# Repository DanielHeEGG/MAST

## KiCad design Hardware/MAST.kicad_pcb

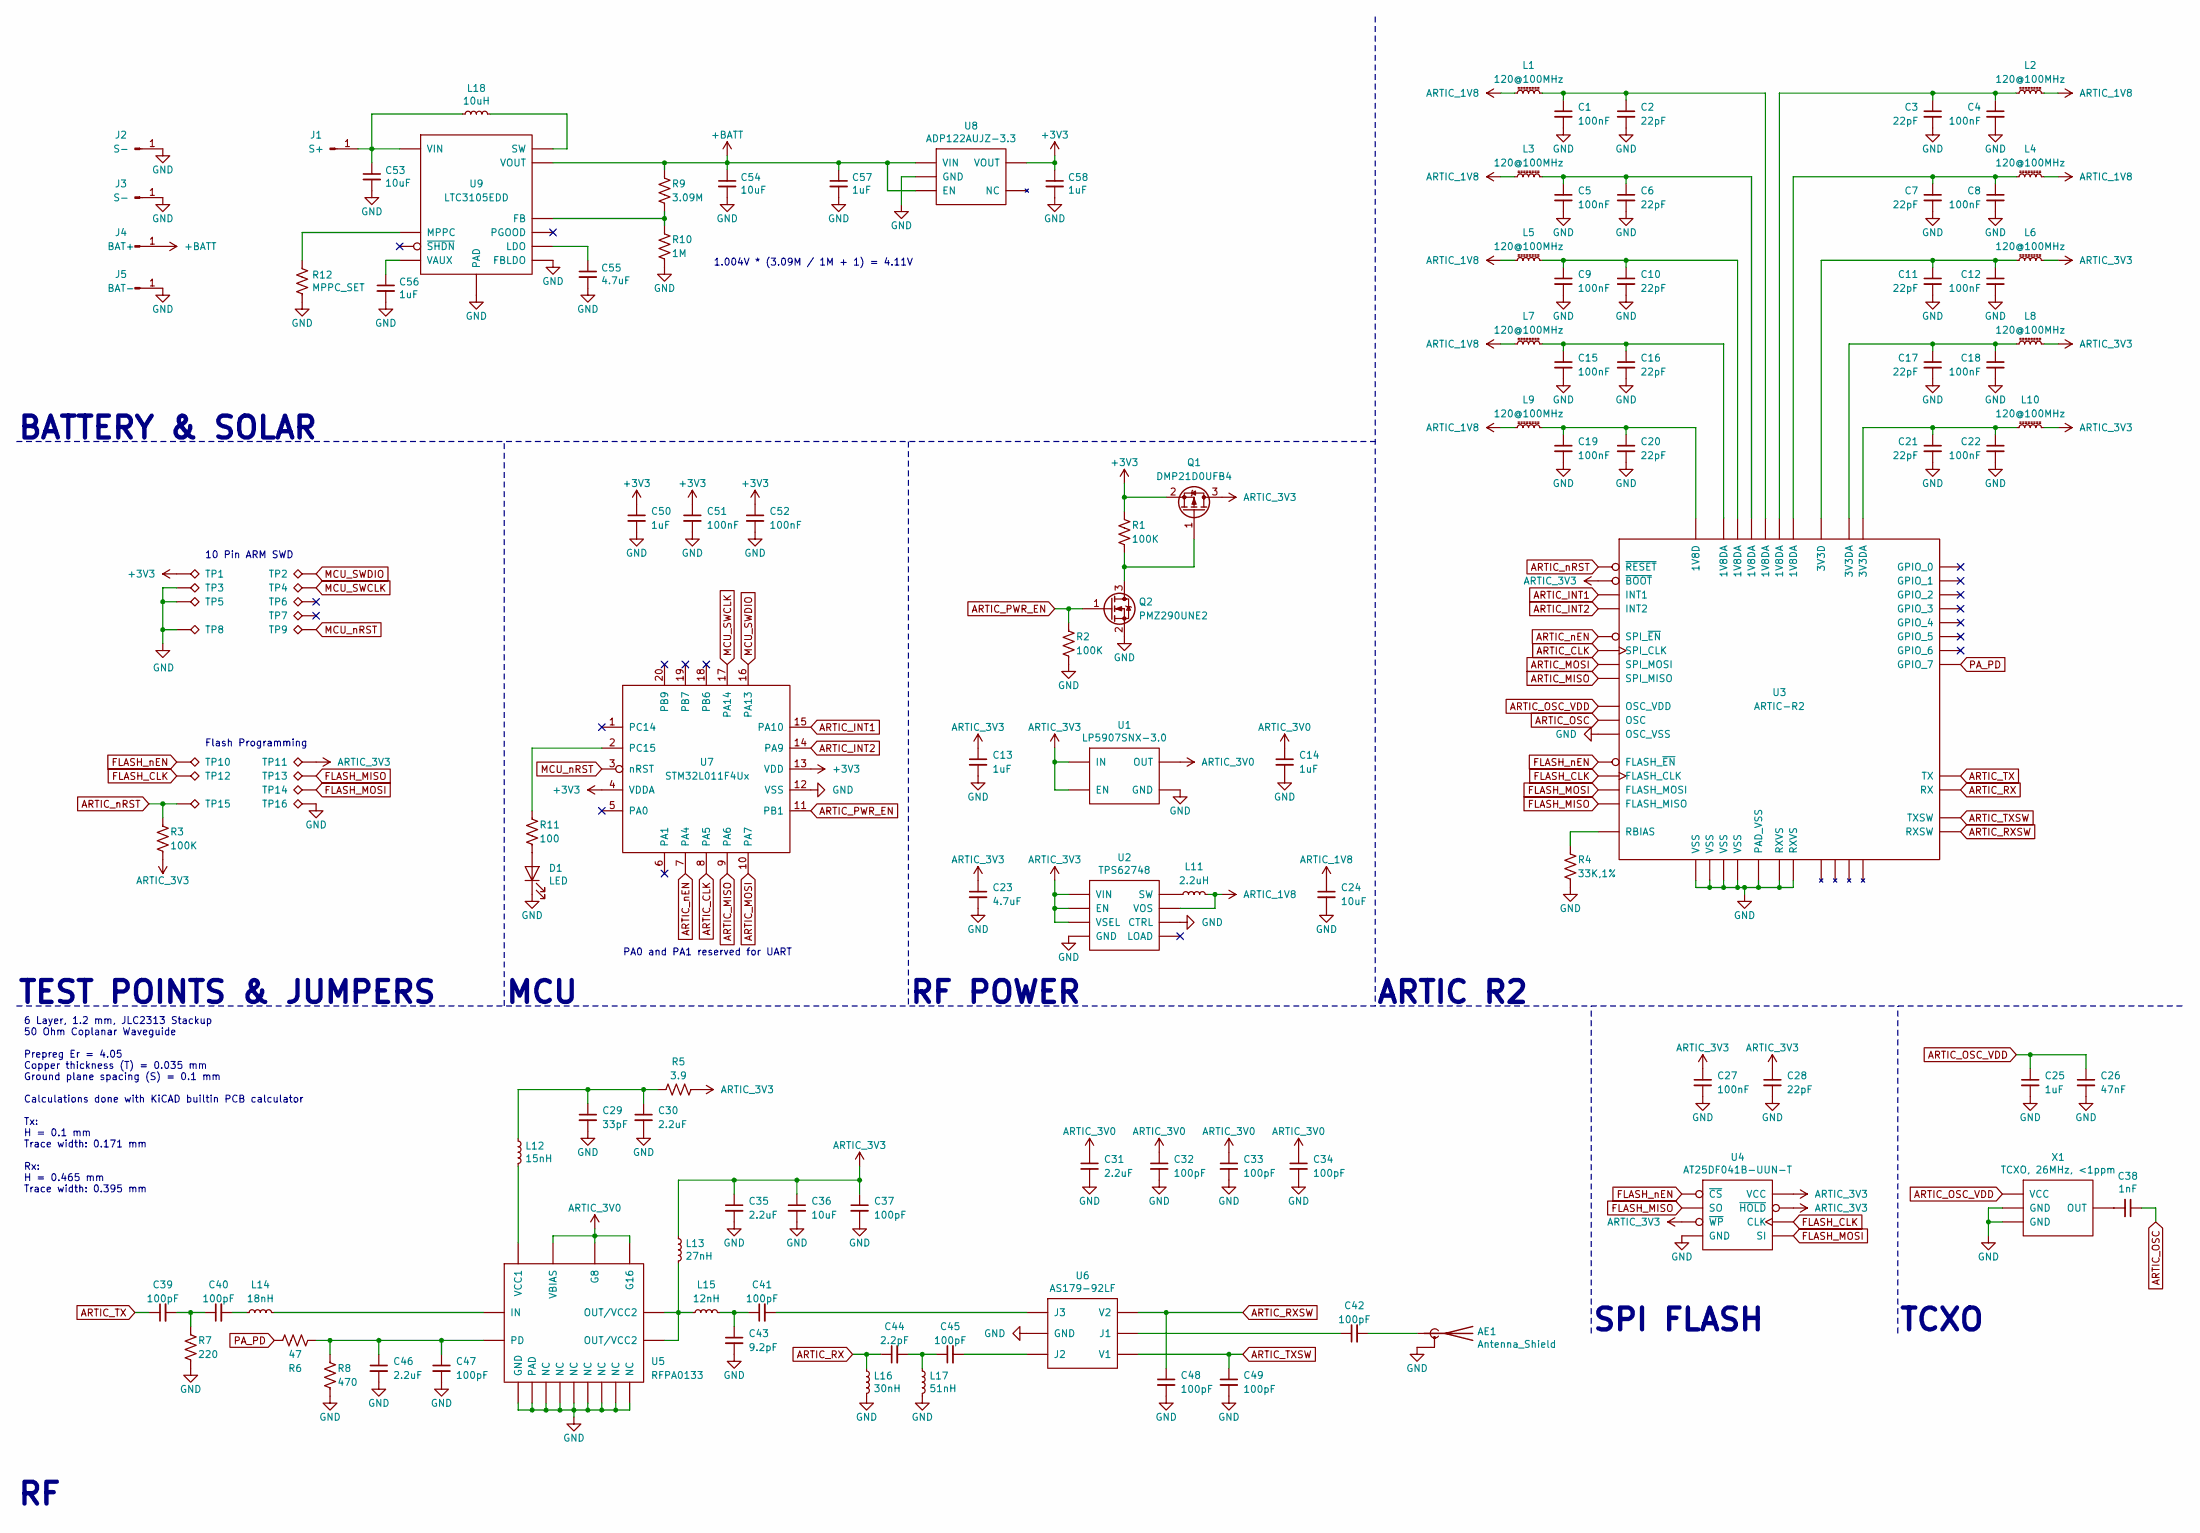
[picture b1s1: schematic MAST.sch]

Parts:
AE1: Antenna_Shield; U.FL_Hirose_U.FL-R-SMT-1_Vertical; Part# U.FL-R-SMT-1(10); Digikey# H11891TR-ND
C1, C4, C5, C8, C9, C12, C15, C18, C19, C22, C27, C51, C52: 100nF; C_0201_0603Metric; Part# CC0201MRX5R5BB104; LCSC# C277512
C2, C3, C6, C7, C10, C11, C16, C17, C20, C21, C28: 22pF; C_0201_0603Metric; Part# CC0201GRNPO9BN220; Digikey# 311-3681-2-ND
C13, C14, C25, C50, C56, C57, C58: 1uF; C_0201_0603Metric; Part# CC0201MRX5R5BB105; Digikey# 311-1613-2-ND
C23, C55: 4.7uF; C_0402_1005Metric; Part# CC0402KRX5R6BB475; Digikey# 311-3477-2-ND
C24, C36, C53, C54: 10uF; C_0402_1005Metric; Part# CC0402MRX5R6BB106; Digikey# 311-3480-2-ND
C26: 47nF; C_0201_0603Metric; Part# CC0201KRX5R6BB473; Digikey# 13-CC0201KRX5R6BB473TR-ND
C29: 33pF; C_0201_0603Metric; Part# CC0201JRNPO8BN330; Digikey# 311-1381-2-ND
C30, C31, C35, C46: 2.2uF; C_0402_1005Metric; Part# CC0402MRX5R6BB225; Digikey# 311-1733-2-ND
C32, C33, C34, C37, C39, C40, C41, C42, C45, C47, C48, C49: 100pF; C_0201_0603Metric; Part# CC0201JRNPO8BN101; Digikey# 311-1382-2-ND
C38: 1nF; C_0201_0603Metric; Part# CC0201KRX7R7BB102; Digikey# 311-1399-2-ND
C43: 9.2pF; C_0201_0603Metric; Part# GJM0335C1E9R2CB01D; Digikey# 490-17292-2-ND
C44: 2.2pF; C_0201_0603Metric; Part# CC0201BRNPO8BN2R2; Digikey# 311-3289-2-ND
D1: LED; LED_0402_1005Metric; Part# 16-213/SURC/S530-A3/TR8; LCSC# C136765
J1: S+; EP_5x2mm
J2, J3: S-; EP_3x2mm
J4: BAT+; EP_3x2mm
J5: BAT-; EP_3x2mm
L1, L2, L3, L4, L5, L6, L7, L8, L9, L10: 120@100MHz; L_0201_0603Metric; Part# BLM03AG121SN1D; Digikey# 490-2557-2-ND
L11: 2.2uH; L_0805_2012Metric; Part# LQM21PN2R2MC0D; Digikey# 490-4994-2-ND
L12: 15nH; L_0201_0603Metric; Part# LQP03TG15NJ02D; Digikey# 490-12895-2-ND
L13: 27nH; L_0201_0603Metric; Part# LQP03TG27NJ02D; Digikey# 490-12942-2-ND
L14: 18nH; L_0201_0603Metric; Part# LQP03TG18NJ02D; Digikey# 490-12896-2-ND
L15: 12nH; L_0201_0603Metric; Part# LQP03TG12NJ02D; Digikey# 490-12894-2-ND
L16: 30nH; L_0201_0603Metric; Part# LQP03TN30NH02D; Digikey# 490-13005-2-ND
L17: 51nH; L_0201_0603Metric; Part# LQP03TN51NH02D; Digikey# 490-13014-2-ND
L18: 10uH; L_0805_2012Metric; Part# LQM21FN100M80L; Digikey# 490-6682-2-ND
Q1: DMP21D0UFB4; SOT-883; Part# DMP21D0UFB4-7B; Digikey# DMP21D0UFB4-7BDITR-ND
Q2: PMZ290UNE2; SOT-883; Part# PMZ290UNE2YL; Digikey# 1727-2233-2-ND
R1, R2, R3: 100K; R_0201_0603Metric; Part# AC0201FR-07100KL; Digikey# YAG3411TR-ND
R4: 33K,1%; R_0201_0603Metric; Part# RC0201FR-0733KL; Digikey# YAG2282TR-ND
R5: 3.9; R_0402_1005Metric; Part# RC0402FR-073R9L; Digikey# 13-RC0402FR-073R9LTR-ND
R6: 47; R_0402_1005Metric; Part# RC0402FR-0747RL; Digikey# 311-47.0LRTR-ND
R7: 220; R_0201_0603Metric; Part# RC0201FR-07220KL; Digikey# YAG2277TR-ND
R8: 470; R_0402_1005Metric; Part# RC0402FR-07470RL; Digikey# 311-470LRTR-ND
R9: 3.09M; R_0201_0603Metric; Part# RC0201FR-073M09L; Digikey# RC0201FR-073M09L-ND
R10: 1M; R_0201_0603Metric; Part# RC0201FR-071ML; Digikey# 311-1MMTR-ND
R11: 100; R_0402_1005Metric; Part# RC0402JR-07100RL; Digikey# 311-100JRTR-ND
R12: MPPC_SET; R_0603_1608Metric
TP1, TP2, TP3, TP4, TP5, TP6, TP7, TP8, TP9, TP10, TP11, TP12, TP13, TP14, TP15, TP16: TestPoint
U1: LP5907SNX-3.0; Texas_X2SON-4_1x1mm_P0.65mm; Part# LP5907SNX-3.0/NOPB; Digikey# 296-39065-2-ND
U2: TPS62748; Texas_DSBGA-8_0.9x1.9mm_Layout2x4_P0.5mm; Part# TPS62748YFPT; Digikey# 296-43000-2-ND
U3: ARTIC-R2; QFN-48-1EP_7x7mm_P0.5mm_EP5.6x5.6mm
U4: AT25DF041B-UUN-T; WLCSP-8_1.58x1.63x0.35mm_Layout3x5_P0.35x0.4mm_Ball0.25mm_P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
U5: RFPA0133; QFN-16-1EP_3x3mm_P0.5mm_EP1.7x1.7mm; Part# RFPA0133TR7; LCSC# C470930
U6: AS179-92LF; SOT-363_SC-70-6; Part# AS179-92LF; Digikey# 863-1003-2-ND
U7: STM32L011F4Ux; ST_UFQFPN-20_3x3mm_P0.5mm; Part# STM32L011F4U6TR; Digikey# 497-17478-2-ND
U8: ADP122AUJZ-3.3; TSOT-23-5; Part# ADP122AUJZ-3.3-R7; Digikey# ADP122AUJZ-3.3-R7TR-ND
U9: LTC3105EDD; DFN-10-1EP_3x3mm_P0.5mm_EP1.65x2.38mm; Part# LTC3105EDD#TRPBF; Digikey# LTC3105EDD#TRPBFTR-ND
X1: TCXO, 26MHz, <1ppm; Crystal_SMD_2016-4Pin_2.0x1.6mm; Part# ECS-TXO-20CSMV-260-AY-TR; Digikey# 50-ECS-TXO-20CSMV-260-AY-TR-ND

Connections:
+3V3: C50.1, C51.1, C52.1, C58.1, Q1.2 (S), R1.1, TP1.1, U7.4 (VDDA), U7.13 (VDD), U8.5 (VOUT)
+BATT: C54.1, C57.1, J4.1, R9.2, U8.1 (VIN), U8.3 (EN), U9.9 (VOUT)
ARTIC_1V8: C24.1, L1.1, L2.1, L3.1, L4.1, L5.1, L7.1, L9.1, L11.2, U2.C2 (VOS)
ARTIC_3V0: C14.1, C31.1, C32.1, C33.1, C34.1, U1.1 (OUT), U5.12 (G8), U5.13 (G16), U5.16 (VBIAS)
ARTIC_3V3: C13.1, C23.1, C27.1, C28.1, C35.1, C36.1, C37.1, L6.1, L8.1, L10.1, L13.1, Q1.3 (D), R3.2, R5.1, TP11.1, U1.3 (EN), U1.4 (IN), U2.A2 (VIN), U2.B1 (EN), U2.C1 (VSEL), U3.46 (~BOOT), U4.A1 (VCC), U4.C1 (~HOLD), U4.E3 (~WP)
ARTIC_CLK: U3.3 (SPI_CLK), U7.8 (PA5)
ARTIC_INT1: U3.47 (INT1), U7.15 (PA10)
ARTIC_INT2: U3.48 (INT2), U7.14 (PA9)
ARTIC_MISO: U3.5 (SPI_MISO), U7.9 (PA6)
ARTIC_MOSI: U3.4 (SPI_MOSI), U7.10 (PA7)
ARTIC_OSC: C38.1, U3.38 (OSC)
ARTIC_OSC_VDD: C25.1, C26.1, U3.37 (OSC_VDD), X1.4 (VCC)
ARTIC_PWR_EN: Q2.1 (G), R2.1, U7.11 (PB1)
ARTIC_RX: C44.1, L16.1, U3.26 (RX)
ARTIC_RXSW: C48.1, U3.22 (RXSW), U6.6 (V2)
ARTIC_TX: C39.1, U3.34 (TX)
ARTIC_TXSW: C49.1, U3.21 (TXSW), U6.4 (V1)
ARTIC_nEN: U3.2 (SPI_~EN), U7.7 (PA4)
ARTIC_nRST: R3.1, TP15.1, U3.1 (~RESET)
FLASH_CLK: TP12.1, U3.12 (FLASH_CLK), U4.E1 (CLK)
FLASH_MISO: TP13.1, U3.14 (FLASH_MISO), U4.C3 (SO)
FLASH_MOSI: TP14.1, U3.13 (FLASH_MOSI), U4.D2 (SI)
FLASH_nEN: TP10.1, U3.15 (FLASH_~EN), U4.A3 (~CS)
GND: AE1.2 (Shield), C1.2, C2.2, C3.2, C4.2, C5.2, C6.2, C7.2, C8.2, C9.2, C10.2, C11.2, C12.2, C13.2, C14.2, C15.2, C16.2, C17.2, C18.2, C19.2, C20.2, C21.2, C22.2, C23.2, C24.2, C25.2, C26.2, C27.2, C28.2, C29.2, C30.2, C31.2, C32.2, C33.2, C34.2, C35.2, C36.2, C37.2, C43.2, C46.2, C47.2, C48.2, C49.2, C50.2, C51.2, C52.2, C53.2, C54.2, C55.2, C56.2, C57.2, C58.2, D1.1 (K), J2.1, J3.1, J5.1, L16.2, L17.2, Q2.2 (S), R2.2, R4.2, R7.1, R8.1, R10.1, R12.2, TP3.1, TP5.1, TP8.1, TP16.1, U1.2 (GND), U1.5, U2.B2 (GND), U2.D1 (CTRL), U3.25 (RXVS), U3.27 (RXVS), U3.29 (VSS), U3.30 (VSS), U3.31 (VSS), U3.32 (VSS), U3.39 (OSC_VSS), U3.49 (PAD_VSS), U4.B2 (GND), U5.1 (NC), U5.2 (GND), U5.4 (NC), U5.5 (NC), U5.7 (NC), U5.8 (NC), U5.11 (NC), U5.15 (NC), U5.17 (PAD), U6.2 (GND), U7.12 (VSS), U8.2 (GND), U9.3 (FBLDO), U9.11 (PAD), X1.1 (GND), X1.2 (GND)
MCU_SWCLK: TP4.1, U7.17 (PA14)
MCU_SWDIO: TP2.1, U7.16 (PA13)
MCU_nRST: TP9.1, U7.3 (nRST)
unnamed: AE1.1 (A), C42.2
unnamed: C1.1, C2.1, L1.2, U3.33 (1V8DA)
unnamed: C3.1, C4.1, L2.2, U3.35 (1V8DA)
unnamed: C5.1, C6.1, L3.2, U3.28 (1V8DA)
unnamed: C7.1, C8.1, L4.2, U3.40 (1V8DA)
unnamed: C9.1, C10.1, L5.2, U3.24 (1V8DA)
unnamed: C11.1, C12.1, L6.2, U3.9 (3V3D)
unnamed: C15.1, C16.1, L7.2, U3.20 (1V8DA)
unnamed: C17.1, C18.1, L8.2, U3.23 (3V3DA)
unnamed: C19.1, C20.1, L9.2, U3.6 (1V8D)
unnamed: C21.1, C22.1, L10.2, U3.36 (3V3DA)
unnamed: C29.1, C30.1, L12.1, R5.2
unnamed: C38.2, X1.3 (OUT)
unnamed: C39.2, C40.1, R7.2
unnamed: C40.2, L14.1
unnamed: C41.1, C43.1, L15.2
unnamed: C41.2, U6.1 (J3)
unnamed: C42.1, U6.5 (J1)
unnamed: C44.2, C45.1, L17.1
unnamed: C45.2, U6.3 (J2)
unnamed: C46.1, C47.1, R6.2, R8.2, U5.6 (PD)
unnamed: C53.1, J1.1, L18.1, U9.6 (VIN)
unnamed: C55.1, U9.2 (LDO)
unnamed: C56.1, U9.10 (VAUX)
unnamed: D1.2 (A), R11.1
unnamed: L11.1, U2.A1 (SW)
unnamed: L12.2, U5.14 (VCC1)
unnamed: L13.2, L15.1, U5.9 (OUT/VCC2), U5.10 (OUT/VCC2)
unnamed: L14.2, U5.3 (IN)
unnamed: L18.2, U9.7 (SW)
unnamed: Q1.1 (G), Q2.3 (D), R1.2
unnamed: R4.1, U3.41 (RBIAS)
unnamed: R9.1, R10.2, U9.1 (FB)
unnamed: R11.2, U7.2 (PC15)
unnamed: R12.1, U9.5 (MPPC)
PA_PD: R6.1, U3.7 (GPIO_7)

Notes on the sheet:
ARTIC R2
SPI FLASH
RF POWER
6 Layer, 1.2 mm, JLC2313 Stackup 50 Ohm Coplanar Waveguide Prepreg Er = 4.05 Copper thickness (T) = 0.035 mm Ground plane spacing (S) = 0.1 mm Calculations done with KiCAD builtin PCB calculator Tx: H = 0.1 mm Trace width: 0.171 mm Rx: H = 0.465 mm Trace width: 0.395 mm
PA0 and PA1 reserved for UART
MCU
TEST POINTS & JUMPERS
TCXO
Flash Programming
10 Pin ARM SWD
BATTERY & SOLAR
1.004V * (3.09M / 1M + 1) = 4.11V

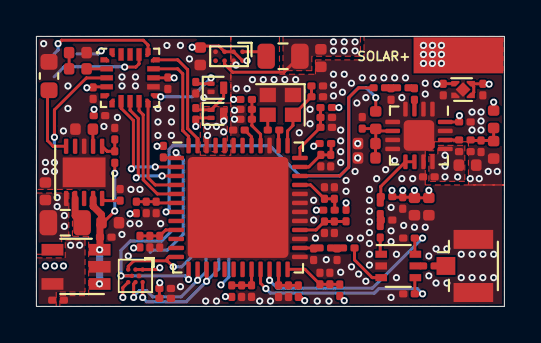
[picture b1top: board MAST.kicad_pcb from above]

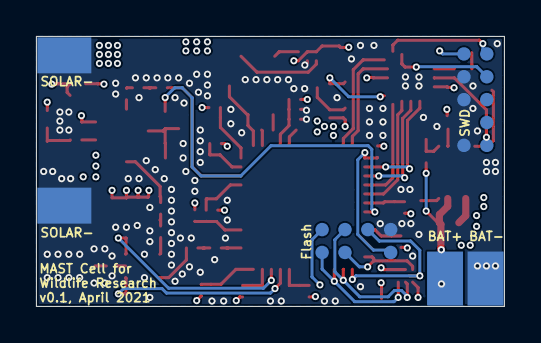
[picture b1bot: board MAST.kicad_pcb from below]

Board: 6 copper layers, 26.0 x 15.0 mm, 123 parts (20 on the bottom side), 63 nets.

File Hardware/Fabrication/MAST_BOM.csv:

"Ref","Value","Footprint","Manufacturer","Part#","Digikey#","LCSC#"
"AE1","Antenna_Shield","Connector_Coaxial:U.FL_Hirose_U.FL-R-SMT-1_Vertical","Hirose","U.FL-R-SMT-1(10)","H11891TR-ND","C434808"
"C1, C4, C5, C8, C9, C12, C15, C18, C19, C22, C27, C51, C52","100nF","Capacitor_SMD:C_0201_0603Metric","Yageo","CC0201MRX5R5BB104","311-3700-2-ND","C277512"
"C2, C3, C6, C7, C10, C11, C16, C17, C20, C21, C28","22pF","Capacitor_SMD:C_0201_0603Metric","Yageo","CC0201GRNPO9BN220","311-3681-2-ND","C526932"
"C13, C14, C25, C50, C56, C57, C58","1uF","Capacitor_SMD:C_0201_0603Metric","Yageo","CC0201MRX5R5BB105","311-1613-2-ND","C272877"
"C23, C55","4.7uF","Capacitor_SMD:C_0402_1005Metric","Yageo","CC0402KRX5R6BB475","311-3477-2-ND","C326586"
"C24, C36, C53, C54","10uF","Capacitor_SMD:C_0402_1005Metric","Yageo","CC0402MRX5R6BB106","311-3480-2-ND","C962143"
"C26","47nF","Capacitor_SMD:C_0201_0603Metric","Yageo","CC0201KRX5R6BB473","13-CC0201KRX5R6BB473TR-ND","C325447"
"C29","33pF","Capacitor_SMD:C_0201_0603Metric","Yageo","CC0201JRNPO8BN330","311-1381-2-ND","C513616"
"C30, C31, C35, C46","2.2uF","Capacitor_SMD:C_0402_1005Metric","Yageo","CC0402MRX5R6BB225","311-1733-2-ND","C541410"
"C32, C33, C34, C37, C39, C40, C41, C42, C45, C47, C48, C49","100pF","Capacitor_SMD:C_0201_0603Metric","Yageo","CC0201JRNPO8BN101","311-1382-2-ND","C389108"
"C38","1nF","Capacitor_SMD:C_0201_0603Metric","Yageo","CC0201KRX7R7BB102","311-1399-2-ND","C541217"
"C43","9.2pF","Capacitor_SMD:C_0201_0603Metric","Murata","GJM0335C1E9R2CB01D","490-17292-2-ND","-"
"C44","2.2pF","Capacitor_SMD:C_0201_0603Metric","Yageo","CC0201BRNPO8BN2R2","311-3289-2-ND","C541170"
"D1","LED","LED_SMD:LED_0402_1005Metric","Everlight","16-213/SURC/S530-A3/TR8","-","C136765"
"L1, L2, L3, L4, L5, L6, L7, L8, L9, L10","120@100MHz","Inductor_SMD:L_0201_0603Metric","Murata","BLM03AG121SN1D","490-2557-2-ND","C97850"
"L11","2.2uH","Inductor_SMD:L_0805_2012Metric","Murata","LQM21PN2R2MC0D","490-4994-2-ND","C98033"
"L12","15nH","Inductor_SMD:L_0201_0603Metric","Murata","LQP03TG15NJ02D","490-12895-2-ND","C237404"
"L13","27nH","Inductor_SMD:L_0201_0603Metric","Murata","LQP03TG27NJ02D","490-12942-2-ND","-"
"L14","18nH","Inductor_SMD:L_0201_0603Metric","Murata","LQP03TG18NJ02D","490-12896-2-ND","C237575"
"L15","12nH","Inductor_SMD:L_0201_0603Metric","Murata","LQP03TG12NJ02D","490-12894-2-ND","C206457"
"L16","30nH","Inductor_SMD:L_0201_0603Metric","Murata","LQP03TN30NH02D","490-13005-2-ND","C206430"
"L17","51nH","Inductor_SMD:L_0201_0603Metric","Murata","LQP03TN51NH02D","490-13014-2-ND","-"
"L18","10uH","Inductor_SMD:L_0805_2012Metric","Murata","LQM21FN100M80L","490-6682-2-ND","C162582"
"Q1","DMP21D0UFB4","Package_TO_SOT_SMD:SOT-883","Diodes","DMP21D0UFB4-7B","DMP21D0UFB4-7BDITR-ND","C155329"
"Q2","PMZ290UNE2","Package_TO_SOT_SMD:SOT-883","Nexperia","PMZ290UNE2YL","1727-2233-2-ND","C478155"
"R1, R2, R3","100K","Resistor_SMD:R_0201_0603Metric","Yageo","AC0201FR-07100KL","YAG3411TR-ND","C226394"
"R4","33K,1%","Resistor_SMD:R_0201_0603Metric","Yageo","RC0201FR-0733KL","YAG2282TR-ND","C155694"
"R5","3.9","Resistor_SMD:R_0402_1005Metric","Yageo","RC0402FR-073R9L","13-RC0402FR-073R9LTR-ND","C137985"
"R6","47","Resistor_SMD:R_0402_1005Metric","Yageo","RC0402FR-0747RL","311-47.0LRTR-ND","C137973"
"R7","220","Resistor_SMD:R_0201_0603Metric","Yageo","RC0201FR-07220KL","YAG2277TR-ND","C142020"
"R8","470","Resistor_SMD:R_0402_1005Metric","Yageo","RC0402FR-07470RL","311-470LRTR-ND","C114877"
"R9","3.09M","Resistor_SMD:R_0201_0603Metric","Yageo","RC0201FR-073M09L","RC0201FR-073M09L-ND","-"
"R10","1M","Resistor_SMD:R_0201_0603Metric","Yageo","RC0201FR-071ML","311-1MMTR-ND","C295786"
"R11","100","Resistor_SMD:R_0402_1005Metric","Yageo","RC0402JR-07100RL","311-100JRTR-ND","C106233"
"U1","LP5907SNX-3.0","Package_SON:Texas_X2SON-4_1x1mm_P0.65mm","TI","LP5907SNX-3.0/NOPB","296-39065-2-ND","C182423"
"U2","TPS62748","Package_BGA:Texas_DSBGA-8_0.9x1.9mm_Layout2x4_P0.5mm","TI","TPS62748YFPT","296-43000-2-ND","C133949"
"U3","ARTIC-R2","Package_DFN_QFN:QFN-48-1EP_7x7mm_P0.5mm_EP5.6x5.6mm","-","-","-","-"
"U4","AT25DF041B-UUN-T","Package_CSP:WLCSP-8_1.58x1.63x0.35mm_Layout3x5_P0.35x0.4mm_Ball0.25mm_Pad0.25mm_NSMD","Adesto","AT25DF041B-UUN-T","1265-1222-2-ND","-"
"U5","RFPA0133","Package_DFN_QFN:QFN-16-1EP_3x3mm_P0.5mm_EP1.7x1.7mm","Qorvo","RFPA0133TR7","-","C470930"
"U6","AS179-92LF","Package_TO_SOT_SMD:SOT-363_SC-70-6","Skyworks","AS179-92LF","863-1003-2-ND","C83422"
"U7","STM32L011F4Ux","Package_DFN_QFN:ST_UFQFPN-20_3x3mm_P0.5mm","ST","STM32L011F4U6TR","497-17478-2-ND","C329283"
"U8","ADP122AUJZ-3.3","Package_TO_SOT_SMD:TSOT-23-5","Analog","ADP122AUJZ-3.3-R7","ADP122AUJZ-3.3-R7TR-ND","C143910"
"U9","LTC3105EDD","Package_DFN_QFN:DFN-10-1EP_3x3mm_P0.5mm_EP1.65x2.38mm","Analog","LTC3105EDD#TRPBF","LTC3105EDD#TRPBFTR-ND","C684029"
"X1","TCXO, 26MHz, <1ppm","Crystal:Crystal_SMD_2016-4Pin_2.0x1.6mm","ECS","ECS-TXO-20CSMV-260-AY-TR","50-ECS-TXO-20CSMV-260-AY-TR-ND","-"

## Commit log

2021-04-18 v0.1
2021-06-30 Organize F.Fab layer for clearer PCB layout
2021-06-30 Increase silkscreen text size & removed some text
2021-07-16 Convert all vias to through hole for cost reduction
2021-07-17 Fix flash chip orientation
2021-07-17 Improve RF 1.8V & 3.3V rail power delivery
2021-07-17 Enable MPPC on solar charger
2021-07-18 Move fabrication files to seperate root folder
